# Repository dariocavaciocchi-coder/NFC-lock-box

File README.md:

# NFC-lock-box

Description:

My project is a lock box that uses rfid/NFC technology to lock and unlock it. It also has an LED to show whether it is locked or unlocked. All you have to do is tap the accepted card and the servo moves to unlock it, remove the lid, take stuff out or put stuff in, close it and tap the card again and the servo will lock the box. I made this project so I could store my most delicate items, without the risk of other people breaking them, as it has happened multiple times before (not on purpose).

Struggles:

I had a few struggles while making this project, but I will only talk about the big one, as I dont want to bore you. I found it very hard to find an effective way to lock and unlock the box effectively, so much so that I changed the mechanism multiple times. At first, I had it to where a servo arm would go in a hole with a wedge and would move to lock/unlock but realised it would be hard to track the circular motion inside that hole, so then I thought of doing a linear locking mechanism. I came up with many ideas, but decided to go with a rack and pinion, as I thought that would be the easiest to implement in the box. I found a template for a rack and pinion online and modified it, so it could fit into the design of my box.

BOM:

A more detailed BOM can be found in the BOM folder

* Xiao RP2040 module X1
* RC522 module set X1
* SG90 servo motor X1
* 3D printed box X1
* M3 Headset inserts X6
* M3 4mm spacer X8
* PCB X1
* LED X1
* 330ohm resistor X1
* 100nF ceramic capacitor X1
* 100microF electrolytic capacitor X1
* 2.54mm pin header X3
* M3 12mm screws X4
* M3 6mm screws X2

Images:

More images can be found in the images folder

.png)
.png)

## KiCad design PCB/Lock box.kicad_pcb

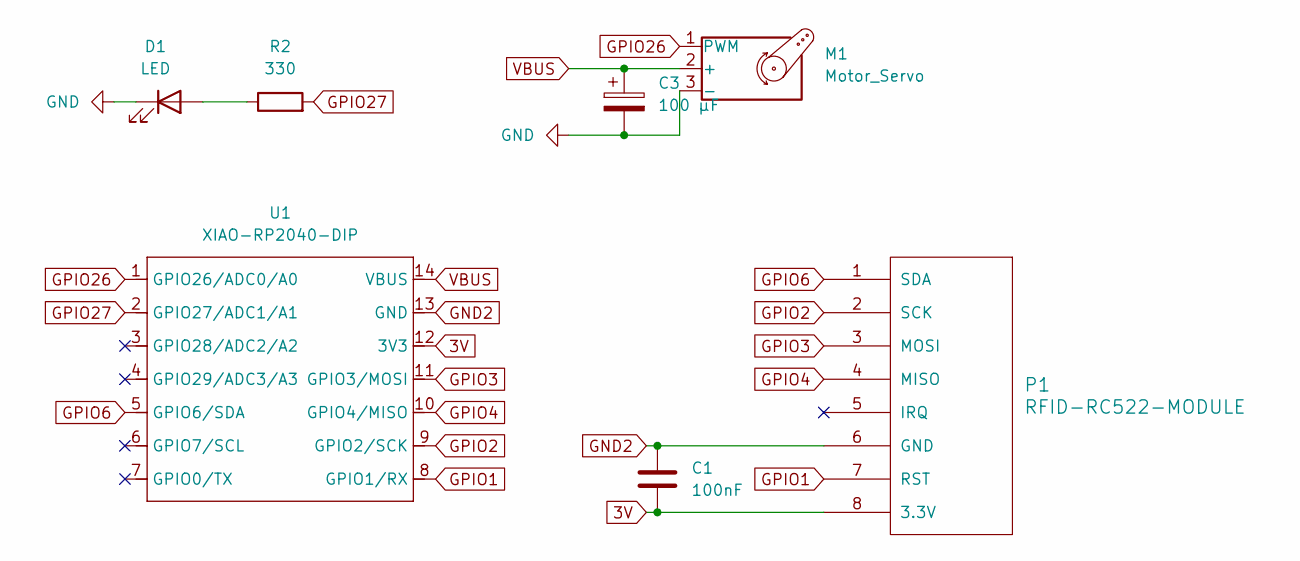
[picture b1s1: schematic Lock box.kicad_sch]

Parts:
C1: 100nF; C_Disc_D5.0mm_W2.5mm_P5.00mm
C3: 100 µF; CP_Radial_D5.0mm_P2.00mm
D1: LED; LED_D5.0mm
M1: Motor_Servo; PinHeader_1x03_P2.54mm_Vertical
P1: RFID-RC522-MODULE; RC522_Module
R2: 330; R_Axial_DIN0207_L6.3mm_D2.5mm_P10.16mm_Horizontal
U1: XIAO-RP2040-DIP

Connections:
3V: C1.2, P1.8 (3.3V), U1.12 (3V3)
GND: C3.2, D1.1 (K), M1.3 (-)
GND2: C1.1, P1.6 (GND), U1.13 (GND)
GPIO1: P1.7 (RST), U1.8 (GPIO1/RX)
GPIO2: P1.2 (SCK), U1.9 (GPIO2/SCK)
GPIO3: P1.3 (MOSI), U1.11 (GPIO3/MOSI)
GPIO4: P1.4 (MISO), U1.10 (GPIO4/MISO)
GPIO6: P1.1 (SDA), U1.5 (GPIO6/SDA)
GPIO26: M1.1 (PWM), U1.1 (GPIO26/ADC0/A0)
GPIO27: R2.2, U1.2 (GPIO27/ADC1/A1)
unnamed: D1.2 (A), R2.1
VBUS: C3.1, M1.2 (+), U1.14 (VBUS)

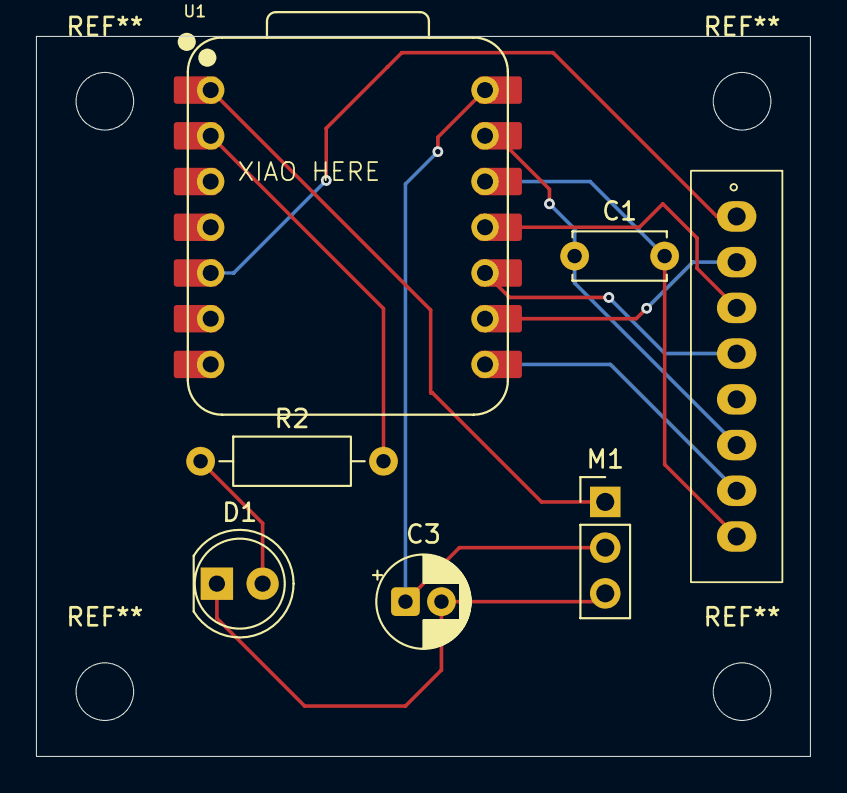
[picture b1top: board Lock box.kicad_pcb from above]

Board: 2 copper layers, 43.0 x 40.0 mm, 7 parts (0 on the bottom side), 12 nets.

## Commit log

2026-03-15 Added all my files
2026-03-15 Fixed BOM and symbols on readme
2026-03-15 Updated images
